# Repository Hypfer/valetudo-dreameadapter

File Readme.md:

# Dreame Adapter PCBs for Valetudo

This repository contains the resources to build the breakout PCBs required for rooting of Dreame Vacuum robots
as documented in the [Valetudo docs](https://valetudo.cloud).

These PCBs are **not meant to be sold**. If you bought one or are aiming to buy one, you've been scammed by a third party
trying to extract value from this project.

I **highly encourage** you not to support such behavior, as - like all value extraction - such actions have devastating results.
The people selling them do not care about you, the project, the world, or me.

In the long term, they made money, and that's all that matters to them.<br/>
If you think about it, you're probably here because you dislike those very business practices.

Therefore, please build the PCB yourself, share it, learn something in the process, connect with like-minded people,
and grow your skillset - rather than giving money to people who thrive on trading better futures for instant gratification and personal gain.

## The PCBs

These are the PCBs (click to jump to their respective readme):
- [Dreame Breakout](./pcbs/dreamebreakout/) - the main one you're looking for (including a step-by-step soldering guide!)
- [Dreame Breakout Breakout](./pcbs/dreamebreakoutbreakout)

Check out the [releases section](https://github.com/Hypfer/valetudo-dreameadapter/releases) to find prebuilt gerber zips
that you can upload to the PCB manufacturer of your choice e.g. JLCPCB, PCBWay, OSHPark, AISLER etc.

While designing these, I made sure to keep them relatively easy to solder by only using THT components so that they
and in turn rooting dreame robots is accessible to more people.

Still, this might not be for everyone. But please keep reading

## Acquiring a PCB

Since we live in an age where there are many cheap hobbyist PCB manufacturing services, the idea behind the PCB is that you
just pick one of those, upload the gerber zip from the releases section and order a set of PCBs for yourself.

As for the components, they're standard parts. Just source them from wherever. Aliexpress, Ebay, Amazon, Digikey, etc.

Within 1-2 weeks or so, you should then receive everything you need and can start soldering the beginner-friendly and easy to solder THT components to the PCB.

## Community building

Because the PCBs are only needed for the initial root (and debugging), the idea is that instead of everyone
having their own, users could share the same PCBs locally with other users so that we not only connect to robots
but also connect to the people around us.

If you
- have built, received or otherwise acquired one of these PCBs and you'd like to help other people root their robots as well

or
- if you're looking for someone with a PCB or maybe general dreame rooting advice near you,

consider joining [the dedicated telegram group](https://t.me/+vuPbtb23w0g0NGIy).

Ideally this would not only enable more people to root their robots but also build a community and provide an opportunity
to meet other people nearby that might share the same interests as you.

We'll see if and how this works out. I think it could be neat

## Acquiring a PCB Kit

If you're located somewhere where no one else has a PCB yet and/or might be unsure on how to order the correct parts,
I have self-soldering kits here in Germany that I tend to ship out to other people within Europe.<br/>
Please note that I'm **not** selling these.

Be aware that preparing and shipping kits is work that takes multiple hours every time that I might not always have at hand.
It's also rather unenjoyable tedious work that I usually do anyway because I enjoy that it brings value to other people.

If you understand that, feel free to ping me via PN to ask about a kit on Telegram (`@NotHypfer`).

Note that this text doesn't state or imply "ping me, and you will for sure receive a kit within 1-3 business days".<br/>
Always remember that I'm just another human being trying to be nice.

Please act accordingly.

## FAQ

### Why can't I order these and use assembly services from e.g. JLCPCB?

Because you should learn how to solder. No, really.<br/>
Soldering is a valuable skill to have in your toolbox and there's no better way to learn something new than being forced
to do so while trying to get something else done.

To make this as easy as possible, everything has been tuned to be easy to solder, only using THT parts.
There's even a step-by-step guide with pictures to completely rule out any confusion or overwhelmement.

This project can do that, because it is entirely luxury fluff. No lives depend on people being able to root their
vacuum robots as quickly and with as little friction as possible.
This is just a hobby and if you're planning on picking up a hobby, you need to actually invest effort into that hobby.

Soldering irons are cheap and there are a lot of guides on the Internets. It is impossible to be able to buy an $800
vacuum robot but don't have any more money to then pick up a used $5 soldering iron or just visit the local makerspace.

<br/>

That said, there are indeed people actually incapable of soldering on their own due to physical disabilities etc.
These are also the people I had in mind when I founded the PCB sharing group so that other users could then help there.

<br/>
Please note that being a mindless consumer is not a disability and thus doesn't warrant any accessibility efforts.
Neither is being a very busy individual that just doesn't have time.

You can't pick up a hobby if you don't have time for that hobby.

### Why are there no pre-soldered PCBs for sale?

Similar to what was stated above, this is a conscious decision to filter out people that don't really care about the
project but just see it as means to an end.
It also filters people who believe that every conceivable problem can be solved with money and not personal growth.

And lastly, it would be a bad idea, because having bought some finished product makes people think that they're a paying
customer which can lead to attitude issues that have no business being anywhere near this project.

### Okay, fine, I'll solder myself. Can you recommend some soldering gear?

Dang, you got me. I'm probably not qualified to recommend stuff, but personally I've been using a MiniWare TS100
running the [Ralim/IronOS](https://github.com/Ralim/IronOS) custom firmware which I bought because
"oh my god a soldering iron that can run a custom firmware". You might be able to relate to that.

It's neat. The digital temperature controls help me greatly and I also quite like how it's so small and can be powered
by any of the many DC power bricks lying around in my living space. Everything I need for soldering fits into a tiny box
that itself fits neatly into an IKEA Billy amongst many other labelled boxes containing small equipment like that.

Nowadays, judging by the IronOS readme, you'd probably want to buy a Pinecil V2 which has DC and USB-C inputs.<br/>
Check the readme of that project for up-to-date recommendations.

You'll then also need some kind of stand for it which will probably be an item the shop you're buying it from
will try to upsell you on anyway. Also, one of these copper sponges to take up excess solder.

For the solder itself, I'm still using lead-based solder. There are serious health considerations there, because there's
no such thing as a healthy amount of lead in your life, but it's also way more forgiving and easier to use than
lead-free solder + flux.<br/>
Don't eat the spool and wash your hands and clean the space afterward.

If you're soldering more stuff, you'll also want to look into fume extraction for which there are off-the-shelf solutions
as well as DIY ideas on the internet.
But just for this one PCB, you can solder outside or probably maybe open a window, point a fan at you and hold your breath?<br/>
Just don't try to actively inhale the solder fumes.

To learn how to solder, consider checking out the [EEVblog tutorial series on YouTube](https://www.youtube.com/watch?v=J5Sb21qbpEQ).

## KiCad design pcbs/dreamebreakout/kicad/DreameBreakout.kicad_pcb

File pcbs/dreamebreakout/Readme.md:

# Dreame Breakout

This breakout PCB takes the 2.0mm pitch 2x8P dreame debug header and breaks that out into a more usable form.

Specifically it provides
- All pins on two 2.54mm pitch headers for use with regular jumper wires etc
- A micro USB socket for flashing stuff via FEL, Livesuit etc.
- A ~~macro USB~~ USB A socket for USB OTG use
- A button to pull BSel to GND to enter FEL
- A jumper to enable USB OTG

**Important:** <br/>
The PCB needs to be manufactured with 1.2mm thickness or else the robot-facing connector won't fit

## Bill of Materials

All the parts required should be available on Aliexpress or similar.

- 1x 2.00mm pitch 2x8P male header
- 2x 2.54mm pitch 1x8P female header
- 1x 6x6mm tactile button
- 1x micro usb port
- 1x usb a port

Optional (can also be done via a regular jumper wire using the larger headers):
- 2x 2.00mm pitch 1x2P male header
- 2x 2.00mm pitch jumper

Keep in mind that there are many different types of USB connectors available on the market.
To make sure that you buy the right parts with the correct footprints, you can use the pictures from the soldering guide below as a reference.

## Assembly

## Soldering guide 

All images in this guide are also links pointing to a higher-res version of them. Make sure to take advantage of that. 

We'll start with an overview shot of all parts you will need.

As the first step, take the robot-facing header and solder it to the PCB.
Do **only a single outer pin first**, then check the alignment and re-align if needed.

Re-aligning with multiple pins soldered will be much harder so make sure to do it correctly.
But also don't worry too much about it as it does not have to be perfect as you can see in the example PCB:

Next up is the Micro USB port. This is probably the scariest part but actually it's not that hard as you can easily access the only five tiny pins.
Place the port on the PCB and use the USB A port to prop up the PCB to align the Micro USB port correctly.

Now, start by soldering the two outer large shield connection points to pin the port in place and then check the alignment. Re-align if needed.
After that, solder the five inner pins. Make sure to not bridge them. If you do have a solder bridge, you can get usually
get rid of it by dragging the soldering iron through the pins as the solder will prefer sticking to the iron instead of the pins.

The next part is the 2-position 2.00mm pitch header for the USB OTG ID jumper.
For that, continue using the USB A port to hold the PCB at the right height and make sure that the header is aligned properly.

Continue by soldering the button to the PCB. Make sure to orient it correctly.
For that, pay close attention to the curvature of its legs in the following picture:

Because of those legs, the button will be fixed in place so you won't be needing the USB A port for alignment anymore.

Next up are the 2.54mm pitch breakout headers. Place them on a flat surface and put the PCB on top like this:

Ensure that they're aligned correctly and then start by soldering just a single leg on the outside on each of them like you did in Step 1 to allow for alignment correction.

When you're happy with the alignment, solder the other end of the connector and then continue to fill in the rest of the pins.

To solder the final USB A connector, you will need something else to prop up the PCB. I've used scissors here.
I'm sure you'll find something that has the right height.

As with the Micro USB connector, start with the two large shield connections on the outside, once again, re-check the alignment and realign as needed.
Then, solder the four inner pins.

Congratulations! You have successfully built a dreame breakout PCB.

If this was helpful to you, there's the option of leaving a tip using [GitHub sponsors](https://github.com/sponsors/Hypfer/).

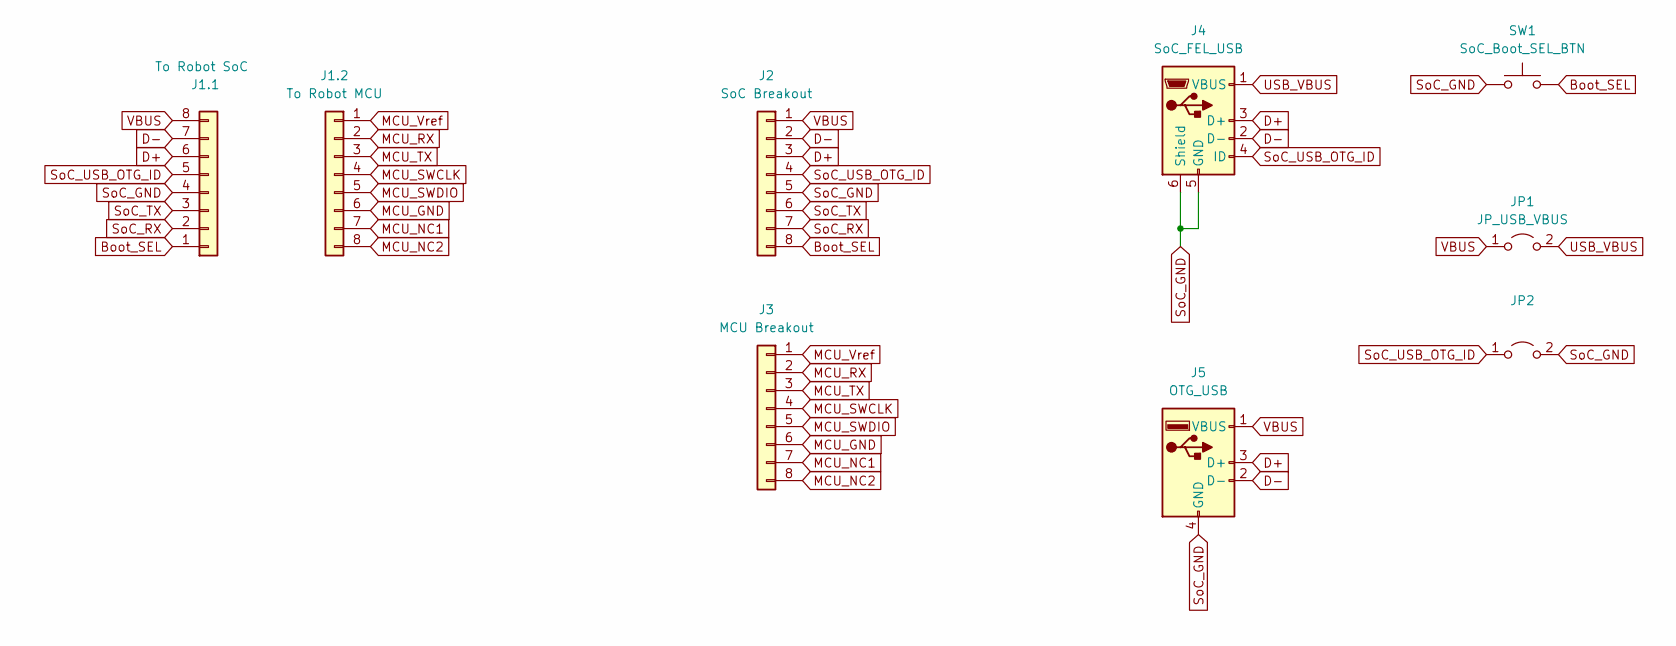
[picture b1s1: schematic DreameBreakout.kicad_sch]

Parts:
J1.1: To Robot SoC; DGI_8_SMDPADS
J1.2: To Robot MCU; DGI_8_SMDPADS
J2: SoC Breakout; PinSocket_1x08_P2.54mm_Vertical
J3: MCU Breakout; PinSocket_1x08_P2.54mm_Vertical
J4: SoC_FEL_USB; USB_Micro-B_Wuerth_614105150721_Vertical
J5: OTG_USB; ONSHORE_USB-A1VSB6
JP1: JP_USB_VBUS; PinSocket_1x02_P2.00mm_Vertical
JP2: (no value)
SW1: SoC_Boot_SEL_BTN; SW_PUSH_6mm

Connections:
Boot_SEL: J1.1.1, J2.8, SW1.2
D+: J1.1.6, J2.3, J4.3 (D+), J5.3 (D+)
D-: J1.1.7, J2.2, J4.2 (D-), J5.2 (D-)
MCU_GND: J1.2.6, J3.6
MCU_NC1: J1.2.7, J3.7
MCU_NC2: J1.2.8, J3.8
MCU_RX: J1.2.2, J3.2
MCU_SWCLK: J1.2.4, J3.4
MCU_SWDIO: J1.2.5, J3.5
MCU_TX: J1.2.3, J3.3
MCU_Vref: J1.2.1, J3.1
SoC_GND: J1.1.4, J2.5, J4.5 (GND), J4.6 (Shield), J5.4 (GND), J5.S1, J5.S2, JP2.2 (B), SW1.1
SoC_RX: J1.1.2, J2.7
SoC_TX: J1.1.3, J2.6
SoC_USB_OTG_ID: J1.1.5, J2.4, J4.4 (ID), JP2.1 (A)
USB_VBUS: J4.1 (VBUS), JP1.2 (B)
VBUS: J1.1.8, J2.1, J5.1 (VBUS), JP1.1 (A)

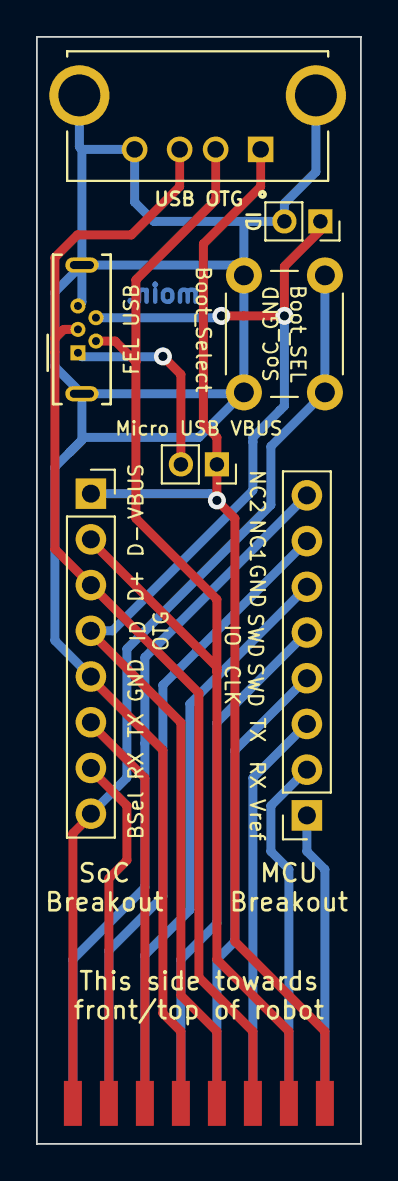
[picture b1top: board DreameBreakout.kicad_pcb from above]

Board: 2 copper layers, 18.0 x 61.5 mm, 9 parts (1 on the bottom side), 17 nets.

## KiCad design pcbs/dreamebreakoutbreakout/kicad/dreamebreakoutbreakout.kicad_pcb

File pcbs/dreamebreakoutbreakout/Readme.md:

# Dreame Breakout Breakout

On some new robots such as the Dreame L10S Ultra, the debug port is rotated so that the lidar tower cover collides
with the headers on the regular Dreame Breakout PCB.

This breakout breakout solves that problem in a way that greatly amuses me.

**Important:** <br/>
The PCB needs to be manufactured with 1.2mm thickness or else the robot-facing connector won't fit

## Bill of Materials

All the parts required should be available on Aliexpress or similar

- 1x 2.00mm pitch 2x8P female header
- 1x 2.00mm pitch 2x8P male header

## Assembly

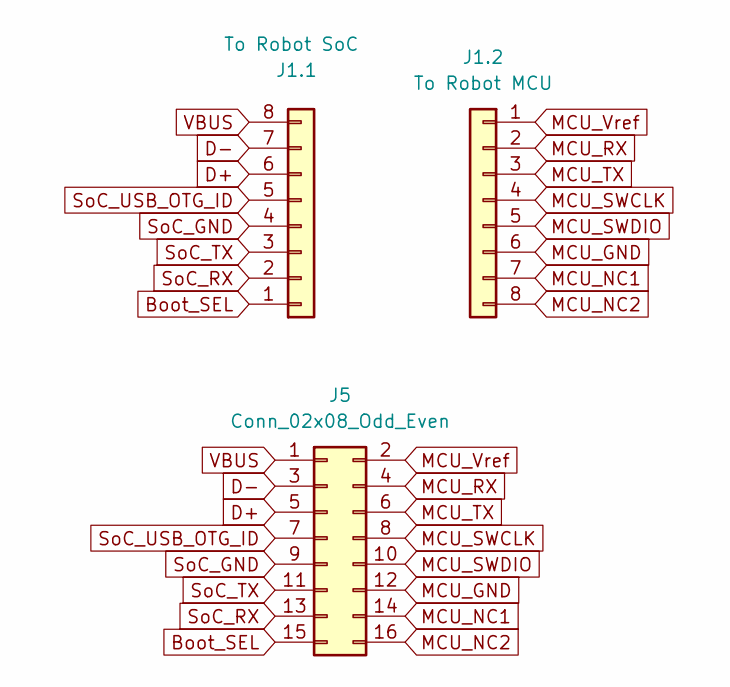
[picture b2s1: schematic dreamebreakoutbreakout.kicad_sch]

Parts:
J1.1: To Robot SoC; DGI_8_SMDPADS
J1.2: To Robot MCU; DGI_8_SMDPADS
J5: Conn_02x08_Odd_Even; PinSocket_2x08_P2.00mm_Vertical

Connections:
Boot_SEL: J1.1.1, J5.15
D+: J1.1.6, J5.5
D-: J1.1.7, J5.3
MCU_GND: J1.2.6, J5.12
MCU_NC1: J1.2.7, J5.14
MCU_NC2: J1.2.8, J5.16
MCU_RX: J1.2.2, J5.4
MCU_SWCLK: J1.2.4, J5.8
MCU_SWDIO: J1.2.5, J5.10
MCU_TX: J1.2.3, J5.6
MCU_Vref: J1.2.1, J5.2
SoC_GND: J1.1.4, J5.9
SoC_RX: J1.1.2, J5.13
SoC_TX: J1.1.3, J5.11
SoC_USB_OTG_ID: J1.1.5, J5.7
VBUS: J1.1.8, J5.1

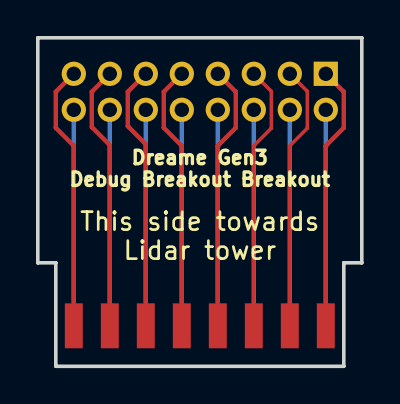
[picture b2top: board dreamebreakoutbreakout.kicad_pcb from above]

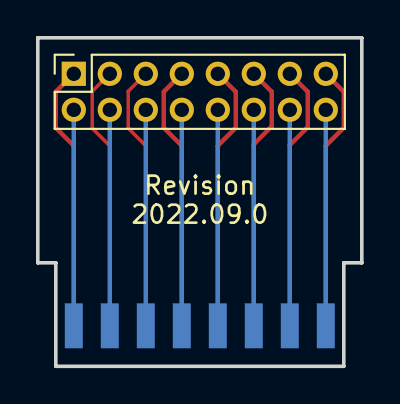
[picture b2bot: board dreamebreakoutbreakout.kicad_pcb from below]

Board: 2 copper layers, 18.0 x 18.2 mm, 3 parts (2 on the bottom side), 16 nets.

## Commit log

2023-08-06 Initial import
2023-08-06 Add note on PCB thickness
2023-08-14 Update Readme.md
    keep up the good work Hypfer! 👍
    Corrected some grammar, added a few words for clarification.
2023-08-15 Add dreamebreakout soldering guide
2023-08-17 Add hint
2023-08-19 docs: clarify USBs are vertical, through hole mount
2023-08-19 Add another hint
2023-11-06 Add FAQ
2023-11-08 Add soldering gear FAQ entry
2023-11-08 Update soldering gear FAQ entry
2024-01-03 Changed size of plated slots for microUSB to 0.45mm so PCBWay will accept it without errors
2024-10-15 Fix license
2024-10-16 Add note
